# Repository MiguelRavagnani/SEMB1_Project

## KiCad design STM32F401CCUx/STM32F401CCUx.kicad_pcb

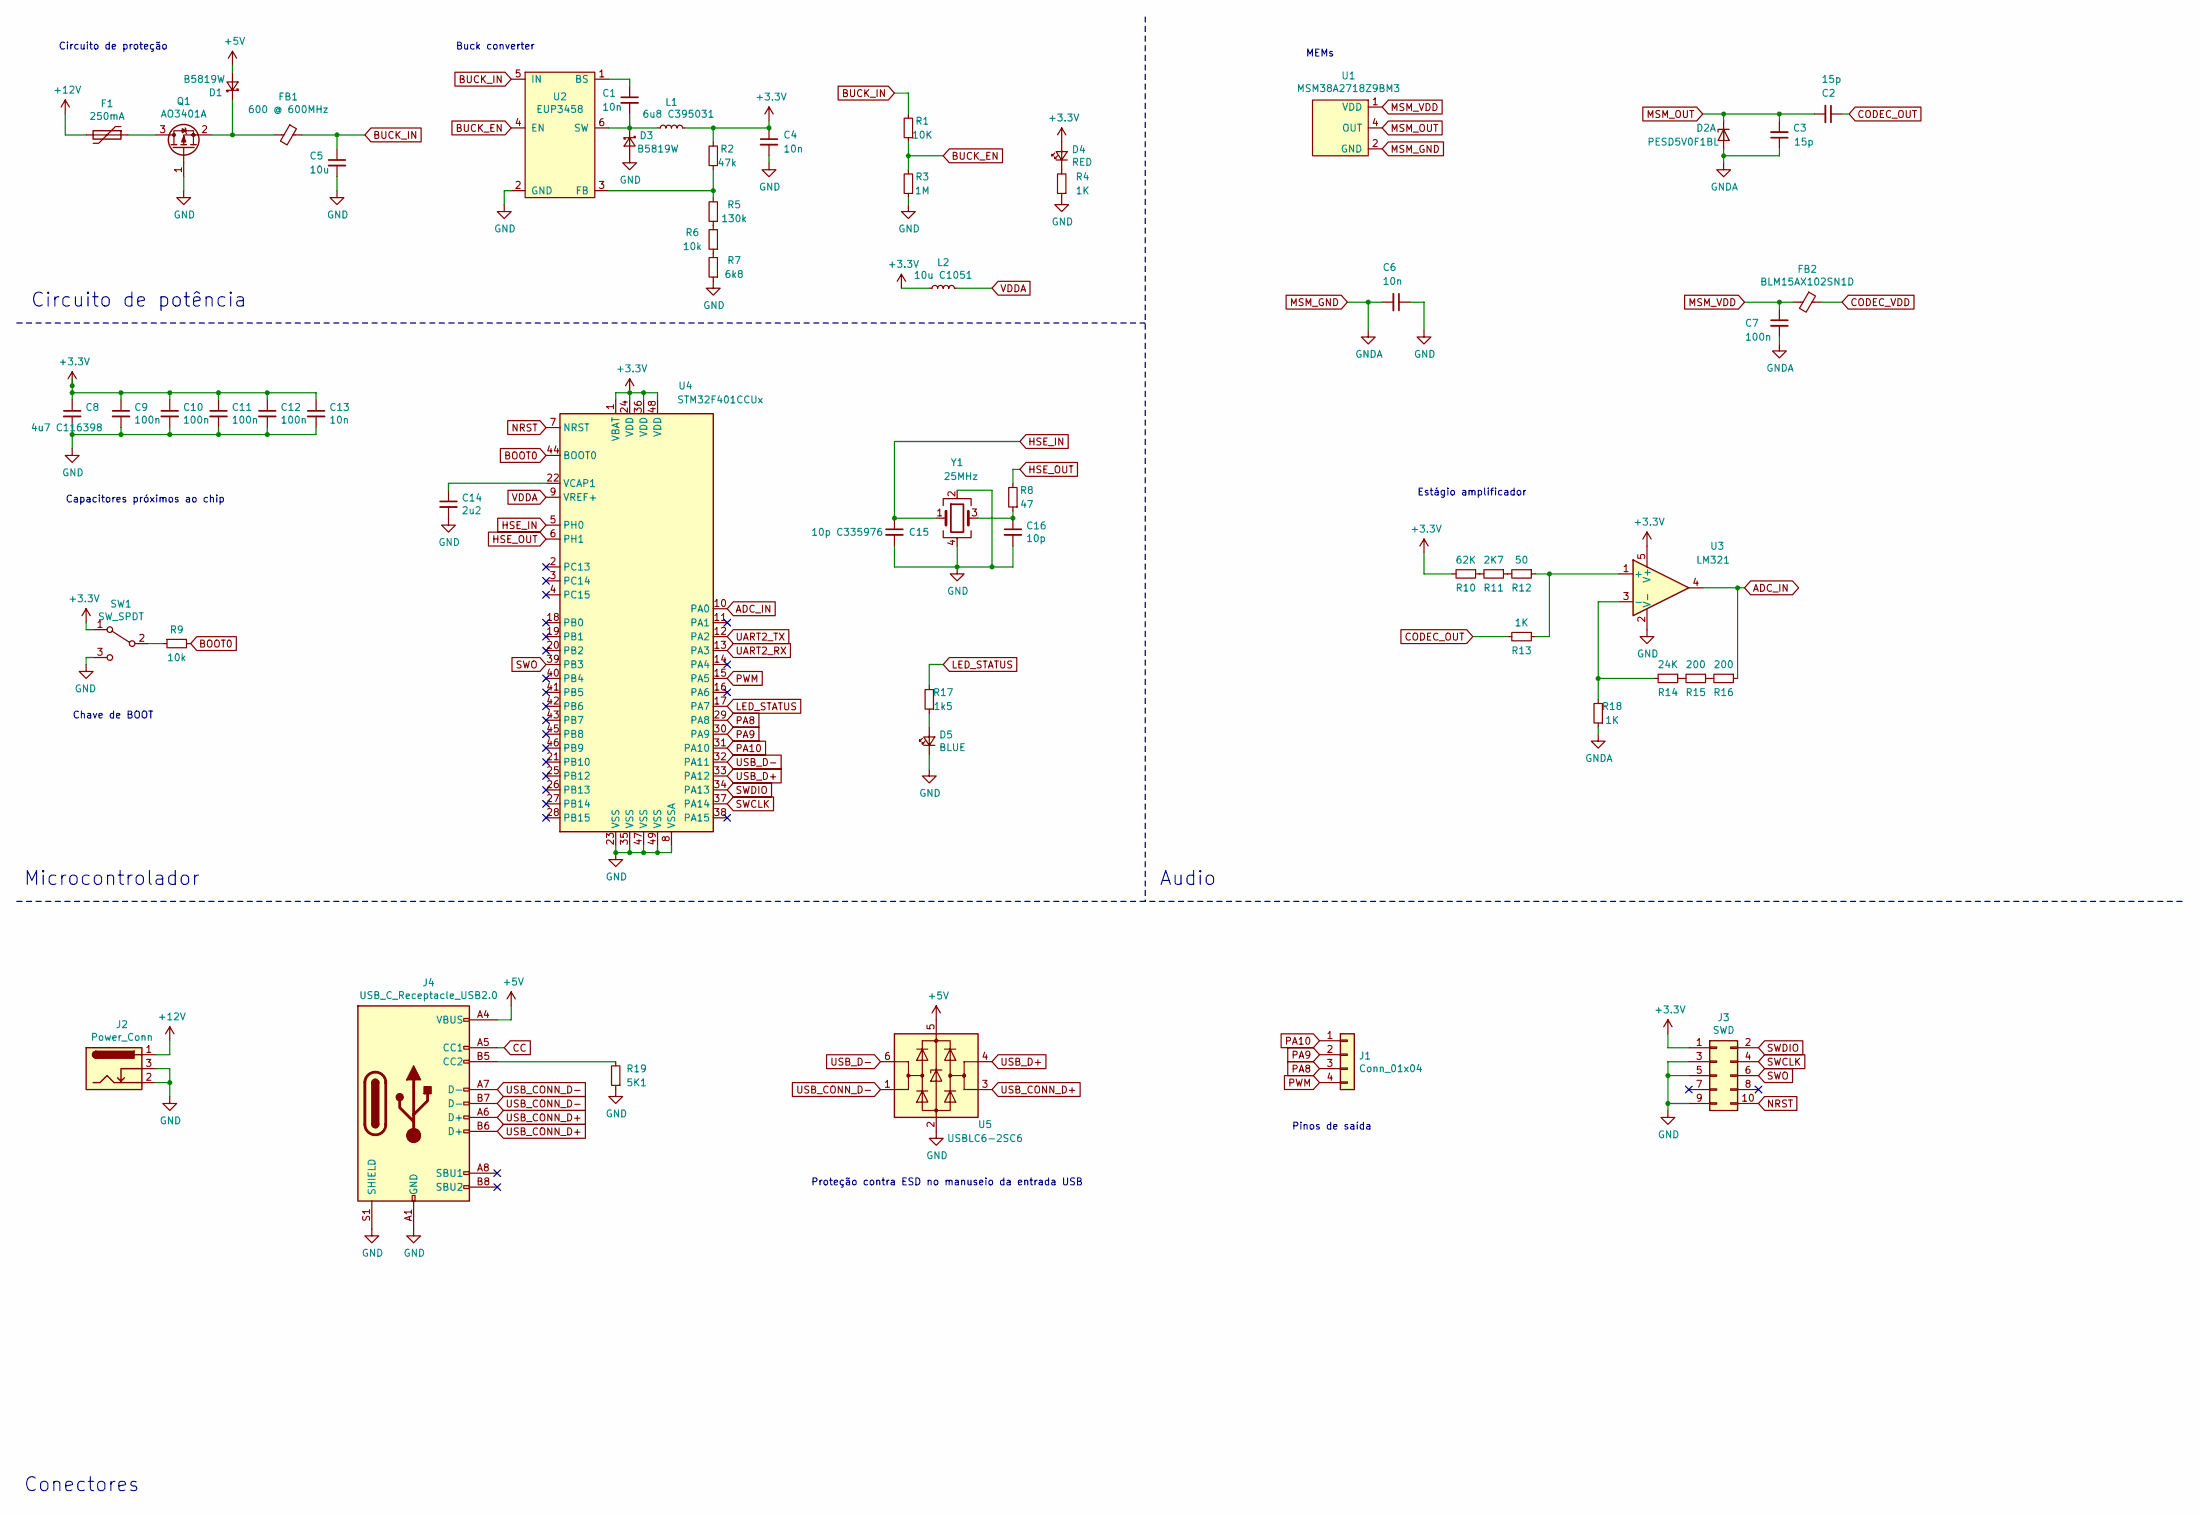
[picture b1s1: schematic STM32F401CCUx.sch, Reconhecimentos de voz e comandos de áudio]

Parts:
C1, C4, C6, C13: 10n; C_0402_1005Metric
C2, C3: 15p; C_0402_1005Metric
C5: 10u; C_0402_1005Metric
C7: 100n; C_0603_1608Metric
C8: 4u7 C116398; CP_Elec_4x5.3
C9, C10, C11, C12: 100n; C_0603_1608Metric_Pad1.05x0.95mm_HandSolder
C14: 2u2; CP_Elec_4x5.7
C15: 10p C335976; C_0402_1005Metric
C16: 10p; C_0402_1005Metric
D1, D3: B5819W; D_SOD-123
D2: PESD5V0F1BL; SOT-666
D4: RED; D_0402_1005Metric
D5: BLUE; D_0402_1005Metric
F1: 250mA; FUSE-TH_L22.6-W9.0
FB1: 600 @ 600MHz; R_0805_2012Metric_Pad1.15x1.40mm_HandSolder
FB2: BLM15AX102SN1D; R_0805_2012Metric_Pad1.15x1.40mm_HandSolder
J1: Conn_01x04; PinHeader_1x04_P2.54mm_Horizontal
J2: Power_Conn; BarrelJack_Horizontal
J3: SWD; PinHeader_2x05_P2.54mm_Horizontal
J4: USB_C_Receptacle_USB2.0; USB_C_Receptacle_HRO_TYPE-C-31-M-12
L1: 6u8 C395031; L_1206_3216Metric
L2: 10u C1051; L_1206_3216Metric
Q1: AO3401A; SOT-23
R1: 10K; R_1206_3216Metric
R2: 47k; R_1206_3216Metric
R3: 1M; R_0805_2012Metric
R4, R13, R18: 1K; R_0805_2012Metric
R5: 130k; R_1206_3216Metric
R6: 10k; R_1206_3216Metric
R7: 6k8; R_1206_3216Metric
R8: 47; R_0805_2012Metric
R9: 10k; R_0805_2012Metric
R10: 62K; R_0805_2012Metric
R11: 2K7; R_0805_2012Metric
R12: 50; R_0805_2012Metric
R14: 24K; R_0805_2012Metric
R15, R16: 200; R_0805_2012Metric
R17: 1k5; R_0805_2012Metric
R19: 5K1; R_0402_1005Metric
SW1: SW_SPDT; SW_SPDT_PCM12
U1: MSM38A2718Z9BM3; MEMS38A
U2: EUP3458; SOT-23-6_Handsoldering
U3: LM321; SOT-23-5
U4: STM32F401CCUx; QFN-48-1EP_7x7mm_P0.5mm_EP5.6x5.6mm
U5: USBLC6-2SC6; SOT-23-6
Y1: 25MHz; Crystal_SMD_3225-4Pin_3.2x2.5mm_HandSoldering

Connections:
+3V3: C4.1, C8.1, C9.1, C10.1, C11.1, C12.1, C13.1, D4.2 (A), J3.1, L1.2, L2.1, R2.2, R10.2, SW1.1 (A), U3.5 (V+), U4.1 (VBAT), U4.24 (VDD), U4.36 (VDD), U4.48 (VDD)
+5V: D1.2 (A), J4.A4 (VBUS), J4.A9 (VBUS), J4.B4 (VBUS), J4.B9 (VBUS), U5.5 (VBUS)
+12V: F1.2, J2.1
ADC_IN: R16.1, U3.4, U4.10 (PA0)
BOOT0: R9.2, U4.44 (BOOT0)
BUCK_EN: R1.1, R3.2, U2.4 (EN)
BUCK_IN: C5.1, FB1.1, R1.2, U2.5 (IN)
CC: J4.A5 (CC1)
CODEC_OUT: C2.1, R13.2
CODEC_VDD: FB2.1
GND: C4.2, C5.2, C6.1, C8.2, C9.2, C10.2, C11.2, C12.2, C13.2, C14.2, C15.2, C16.2, D3.2 (A), D5.1 (K), J2.2, J2.3, J3.3, J3.5, J3.9, J4.A1 (GND), J4.A12 (GND), J4.B1 (GND), J4.B12 (GND), J4.S1 (SHIELD), Q1.1 (G), R3.1, R4.1, R7.1, R19.1, SW1.3 (C), U2.2 (GND), U3.2 (V-), U4.8 (VSSA), U4.23 (VSS), U4.35 (VSS), U4.47 (VSS), U4.49 (VSS), U5.2 (GND), Y1.2, Y1.4
HSE_IN: C15.1, U4.5 (PH0), Y1.1
HSE_OUT: R8.2, U4.6 (PH1)
LED_STATUS: R17.2, U4.17 (PA7)
MSM_GND: C3.1, C6.2, C7.2, D2.2 (A), R18.1, U1.2 (GND)
MSM_OUT: C2.2, C3.2, D2.1 (K1), U1.4 (OUT)
MSM_VDD: C7.1, FB2.2, U1.1 (VDD)
NRST: J3.10, U4.7 (NRST)
unnamed: C1.1, U2.1 (BS)
unnamed: C1.2, D3.1 (K), L1.1, U2.6 (SW)
unnamed: C14.1, U4.22 (VCAP1)
unnamed: C16.1, R8.1, Y1.3
unnamed: D1.1 (K), FB1.2, Q1.2 (S)
unnamed: D4.1 (K), R4.2
unnamed: D5.2 (A), R17.1
unnamed: F1.1, Q1.3 (D)
unnamed: J4.B5 (CC2), R19.2
unnamed: R2.1, R5.2, U2.3 (FB)
unnamed: R5.1, R6.2
unnamed: R6.1, R7.2
unnamed: R9.1, SW1.2 (B)
unnamed: R10.1, R11.2
unnamed: R11.1, R12.2
unnamed: R12.1, R13.1, U3.1 (+)
unnamed: R14.1, R15.2
unnamed: R14.2, R18.2, U3.3 (-)
unnamed: R15.1, R16.2
PA8: J1.3, U4.29 (PA8)
PA9: J1.2, U4.30 (PA9)
PA10: J1.1, U4.31 (PA10)
PWM: J1.4, U4.15 (PA5)
SWCLK: J3.4, U4.37 (PA14)
SWDIO: J3.2, U4.34 (PA13)
SWO: J3.6, U4.39 (PB3)
UART2_RX: U4.13 (PA3)
UART2_TX: U4.12 (PA2)
USB_CONN_D+: J4.A6 (D+), J4.B6 (D+), U5.3 (I/O2)
USB_CONN_D-: J4.A7 (D-), J4.B7 (D-), U5.1 (I/O1)
USB_D+: U4.33 (PA12), U5.4 (I/O2)
USB_D-: U4.32 (PA11), U5.6 (I/O1)
VDDA: L2.2, U4.9 (VREF+)

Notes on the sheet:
Circuito de potência
Microcontrolador
Audio
Conectores
Circuito de proteção
Buck converter
MEMs
Estágio amplificador
Chave de BOOT
Capacitores próximos ao chip
Proteção contra ESD no manuseio da entrada USB
Pinos de saída

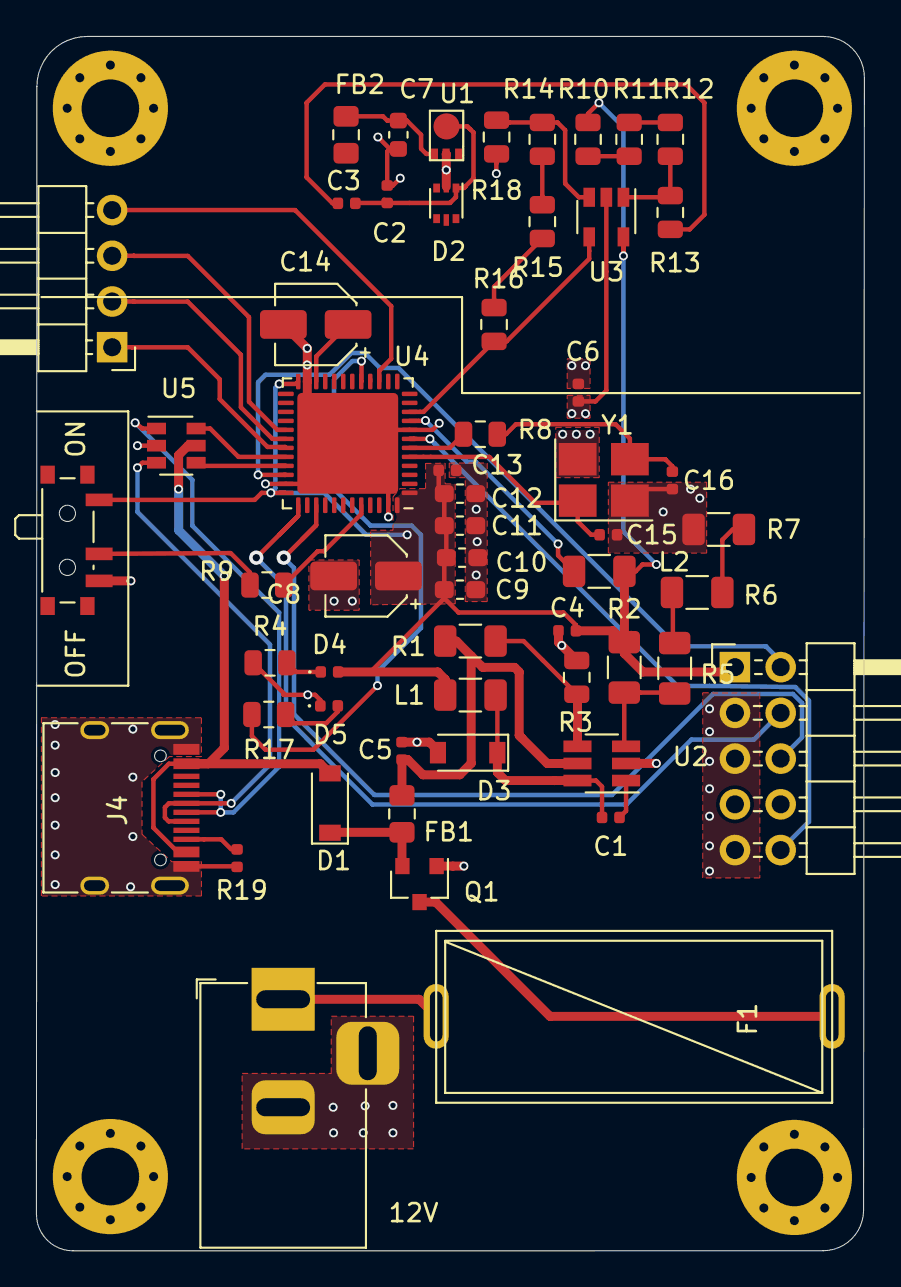
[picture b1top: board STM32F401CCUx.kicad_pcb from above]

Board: 2 copper layers, 46.0 x 67.5 mm, 57 parts (0 on the bottom side), 47 nets.

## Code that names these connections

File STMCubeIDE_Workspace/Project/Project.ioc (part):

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Mcu.UserName=STM32F401CCUx
PH1\ -\ OSC_OUT.Mode=HSE-External-Oscillator
PA11.Mode=Device_Only
RCC.SYSCLKSource=RCC_SYSCLKSOURCE_PLLCLK
PA0-WKUP.Signal=ADCx_IN0
PA13.Signal=SYS_JTMS-SWDIO
PA3.Mode=Asynchronous
PA12.Signal=USB_OTG_FS_DP
PH0\ -\ OSC_IN.Mode=HSE-External-Oscillator
PH0\ -\ OSC_IN.Signal=RCC_OSC_IN
PA5.Signal=S_TIM2_CH1_ETR
RCC.HSE_VALUE=25000000
PH1\ -\ OSC_OUT.Signal=RCC_OSC_OUT
board=custom
PA14.Mode=Serial_Wire
PA13.Mode=Serial_Wire
Mcu.Name=STM32F401C(B-C)Ux
PA2.Signal=USART2_TX
RCC.SYSCLKFreq_VALUE=60000000
Mcu.Package=UFQFPN48
PA12.Mode=Device_Only
PA11.Signal=USB_OTG_FS_DM
PA14.Signal=SYS_JTCK-SWCLK
PA2.Mode=Asynchronous
PA3.Signal=USART2_RX

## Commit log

2021-04-17 Pre Commit
2021-04-28 Audio Amp and USB Power
    Added a pre-amp stage and fixed the USB connections
2021-06-15 Updated PCB
